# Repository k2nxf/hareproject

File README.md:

# hareproject
The hackable audio and real-time effects (H.A.R.E) project

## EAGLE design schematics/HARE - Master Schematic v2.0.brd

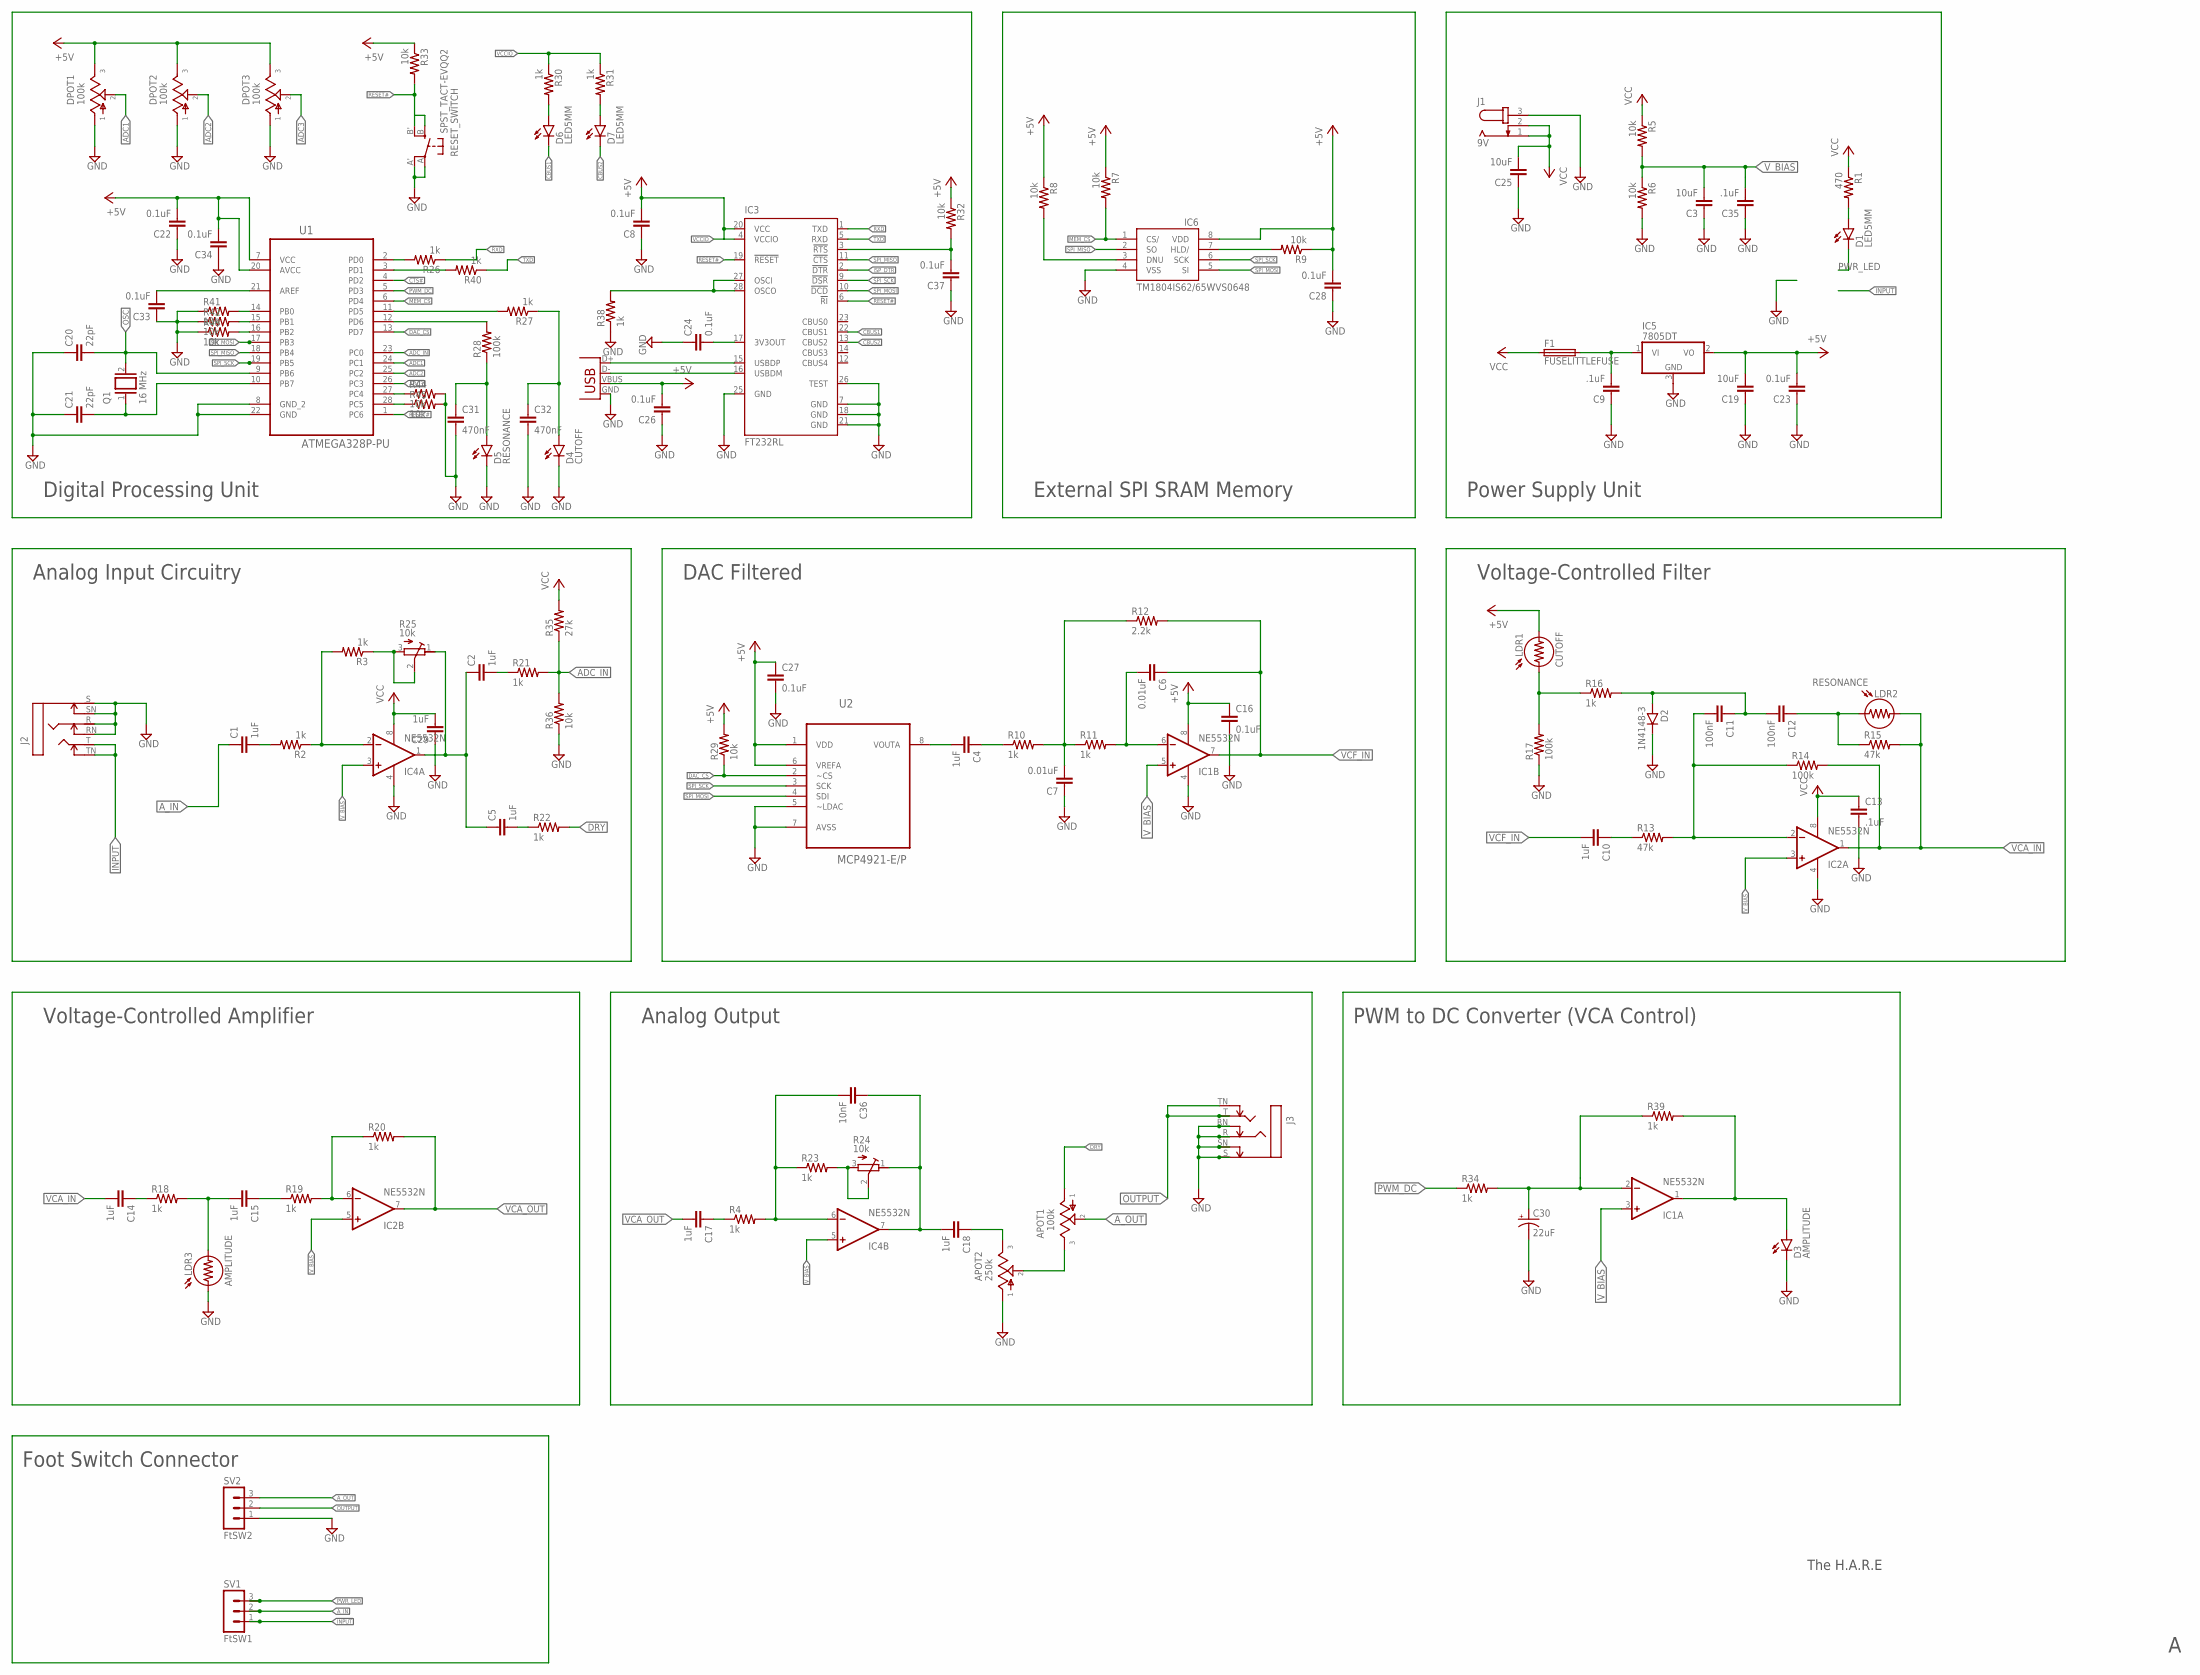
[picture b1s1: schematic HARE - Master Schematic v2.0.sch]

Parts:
APOT1: 100k; 16MM-SQUARE
APOT2: 250k; 16MM-SQUARE
C1, C2, C4, C5, C10, C14, C15, C17, C18, C29: 1uF; C0805K
C3, C19, C25: 10uF; C0805K
C6, C7: 0.01uF; C0805K
C8, C16, C22, C23, C24, C26, C27, C28, C33, C34, C37: 0.1uF; C0805K
C9, C13, C35: .1uF; C0805K
C11, C12: 100nF; C0805K
C20, C21: 22pF; C0805K
C30: 22uF; 050_020_1
C31, C32: 470nF; 072X035
C36: 10nF; C0805K
D1, D6, D7: LED5MM
D2: 1N4148-3; DO35-3
D3: AMPLITUDE; LED5MM
D4: CUTOFF; LED5MM
D5: RESONANCE; LED5MM
DPOT1, DPOT2, DPOT3: 100k; 16MM-SQUARE
F1: FUSELITTLEFUSE; LITTLEFUSE
IC1, IC2, IC4: NE5532N; DIL08
IC3: FT232RL; SSOP28
IC5: 7805DT; TO252
IC6: TM1804IS62/65WVS0648; SO08
J1: 9V; SPC4078
J2, J3: STEREOSW; NMJ6HCD2
LDR1: CUTOFF; LDR338-54C
LDR2: RESONANCE; LDR338-54C
LDR3: AMPLITUDE; LDR338-54C
Q1: 16 MHz; QS
R1: 470; M0805
R2, R3, R4, R10, R11, R16, R18, R19, R20, R21, R22, R23, R26, R27, R30, R31, R34, R38, R39, R40: 1k; R0805
R5, R6, R7, R8, R9: 10k; M0805
R12: 2.2k; R0805
R13, R15: 47k; R0805
R14, R17, R28: 100k; R0805
R24, R25: 10k; RTRIM3314G
R29, R32, R33, R36, R41, R42, R43, R44, R45: 10k; R0805
R35: 27k; R0805
RESET_SWITCH: SPST_TACT-EVQQ2; EVQ-Q2
SV1: FtSW1; MA03-1
SV2: FtSW2; MA03-1
U1: ATMEGA328P-PU; DIP254P762X457-28
U2: MCP4921-E/P; DIP254P762X432-8
X2: USB-B-H

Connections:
+5V: C16.1, C19.2, C22.2, C23.2, C26.2, C27.1, C28.2, C34.2, DPOT1.3, DPOT2.3, DPOT3.3, IC1.8 (V+), IC5.2 (VO), IC6.8 (VDD), LDR1.2, R7.1, R8.1, R9.1, R29.2, R32.1, R33.1, U1.7 (VCC), U1.20 (AVCC), U2.1 (VDD), U2.6 (VREFA), X2.VBUS
+5V1: C33.2, U1.21 (AREF)
ADC1: DPOT1.2, U1.24 (PC1)
ADC2: DPOT2.2, U1.25 (PC2)
ADC3: DPOT3.2, U1.26 (PC3)
ADC_IN: R21.2, R35.1, R36.2, U1.23 (PC0)
A_IN: C1.1, SV1.2
A_OUT: APOT1.2, SV2.3
CBUS1: D6.K (C), IC3.22 (CBUS1)
CBUS2: D7.K (C), IC3.13 (CBUS2)
CTS#: U1.4 (PD2)
DAC_CS: R29.1, U1.13 (PD7), U2.2 (~CS)
DRY: APOT1.1, R22.2
GND: APOT2.1, C3.1, C7.1, C8.1, C9.1, C13.2, C16.2, C19.1, C20.1, C21.1, C22.1, C23.1, C24.1, C25.1, C26.1, C27.2, C28.1, C29.1, C30.-, C31.2, C32.2, C33.1, C34.1, C35.1, C37.1, D2.C, D3.K (C), D4.K (C), D5.K (C), DPOT1.1, DPOT2.1, DPOT3.1, IC1.4 (V-), IC2.4 (V-), IC3.7 (GND), IC3.18 (GND), IC3.21 (GND), IC3.25 (GND), IC3.26 (TEST), IC4.4 (V-), IC5.3 (GND), IC6.4 (VSS), J1.3, J2.R, J2.RN, J2.S, J2.SN, J3.R, J3.RN, J3.S, J3.SN, LDR3.1, R6.2, R17.1, R36.1, R38.1, R41.1, R42.1, R43.1, R44.2, R45.2, RESET_SWITCH.A, RESET_SWITCH.A' (P1), SV2.1, U1.8 (GND_2), U1.22 (GND), U2.5 (~LDAC), U2.7 (AVSS), X2.GND
INPUT: J2.T, J2.TN, SV1.1
ISP_DTR: IC3.2 (!DTR)
MEM_CS: IC6.1 (CS/), R7.2, U1.6 (PD4)
unnamed: D1.A, R1.2
unnamed: IC6.7 (HLD/), R9.2
unnamed: C1.2, R2.2
unnamed: IC4.2 (-IN), R2.1, R3.2
unnamed: C4.2, U2.8 (VOUTA)
unnamed: C4.1, R10.1
unnamed: C5.2, R22.1
unnamed: C30.+, IC1.2 (-IN), R34.2, R39.1
unnamed: C7.2, R10.2, R11.1, R12.1
unnamed: C6.2, IC1.6 (-IN), R11.2
unnamed: IC6.3 (DNU), R8.2
unnamed: D3.A, IC1.1 (OUT), R39.2
unnamed: C10.1, R13.1
unnamed: C11.2, IC2.2 (-IN), R13.2, R14.1
unnamed: C37.2, IC3.3 (!RTS), R32.2
unnamed: C12.1, LDR2.1, R15.1
unnamed: C11.1, C12.2, D2.A, R16.2
unnamed: IC3.27 (OSCI), IC3.28 (OSCO), R38.2
unnamed: LDR1.1, R16.1, R17.2
unnamed: C14.1, R18.1
unnamed: C15.2, LDR3.2, R18.2
unnamed: C15.1, R19.1
unnamed: IC2.6 (-IN), R19.2, R20.1
unnamed: C9.2, F1.2, IC5.1 (VI)
unnamed: R26.2, U1.2 (PD0)
unnamed: C2.2, R21.1
unnamed: C2.1, C5.1, IC4.1 (OUT), R25.1 (E)
unnamed: R40.2, U1.3 (PD1)
unnamed: R41.2, U1.14 (PB0)
unnamed: C17.1, R4.1
unnamed: C36.2, IC4.6 (-IN), R4.2, R23.1
unnamed: R23.2, R24.2 (S), R24.3 (A)
unnamed: C18.2, C36.1, IC4.7 (OUT), R24.1 (E)
unnamed: R42.2, U1.15 (PB1)
unnamed: APOT2.3, C18.1
unnamed: APOT1.3, APOT2.2
unnamed: R43.2, U1.16 (PB2)
unnamed: R3.1, R25.2 (S), R25.3 (A)
unnamed: R44.1, U1.27 (PC4)
unnamed: C21.2, Q1.1, U1.10 (PB7)
unnamed: IC3.15 (USBDP), X2.D+
unnamed: IC3.16 (USBDM), X2.D-
unnamed: C24.2, IC3.17 (3V3OUT)
unnamed: R45.1, U1.28 (PC5)
unnamed: R28.2, U1.12 (PD6)
unnamed: C31.1, D5.A, R28.1
unnamed: R27.2, U1.11 (PD5)
unnamed: C32.1, D4.A, R27.1
unnamed: D6.A, R30.2
unnamed: D7.A, R31.2
OSC: C20.2, Q1.2, U1.9 (PB6)
OUTPUT: J3.T, J3.TN, SV2.2
PWM_DC: R34.1, U1.5 (PD3)
PWR_LED: D1.K (C), SV1.3
RESET#: IC3.6 (!RI), IC3.19 (!RESET), R33.2, RESET_SWITCH.B (S), RESET_SWITCH.B' (S1), U1.1 (PC6)
RXD: IC3.1 (TXD), R26.1
SPI_MISO: IC3.11 (!CTS), IC6.2 (SO), U1.18 (PB4)
SPI_MOSI: IC3.10 (!DCD), IC6.5 (SI), U1.17 (PB3), U2.4 (SDI)
SPI_SCK: IC3.9 (!DSR), IC6.6 (SCK), U1.19 (PB5), U2.3 (SCK)
TXD: IC3.5 (RXD), R40.1
VCA_IN: C14.2, IC2.1 (OUT), LDR2.2, R14.2, R15.2
VCA_OUT: C17.2, IC2.7 (OUT), R20.2
VCC: C13.1, C25.2, C29.2, F1.1, IC2.8 (V+), IC4.8 (V+), J1.1, J1.2, R1.1, R5.1, R35.2
VCCIO: C8.2, IC3.4 (VCCIO), IC3.20 (VCC), R30.1, R31.1
VCF_IN: C6.1, C10.2, IC1.7 (OUT), R12.2
V_BIAS: C3.2, C35.2, IC1.3 (+IN), IC1.5 (+IN), IC2.3 (+IN), IC2.5 (+IN), IC4.3 (+IN), IC4.5 (+IN), R5.2, R6.1

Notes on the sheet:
Power Supply Unit
Digital Processing Unit
Analog Output
Voltage-Controlled Filter
Voltage-Controlled Amplifier
Analog Input Circuitry
DAC Filtered
External SPI SRAM Memory
The H.A.R.E
Foot Switch Connector
PWM to DC Converter (VCA Control)

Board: 2 copper layers, 113 parts (0 on the bottom side), 81 nets, no tracks yet.

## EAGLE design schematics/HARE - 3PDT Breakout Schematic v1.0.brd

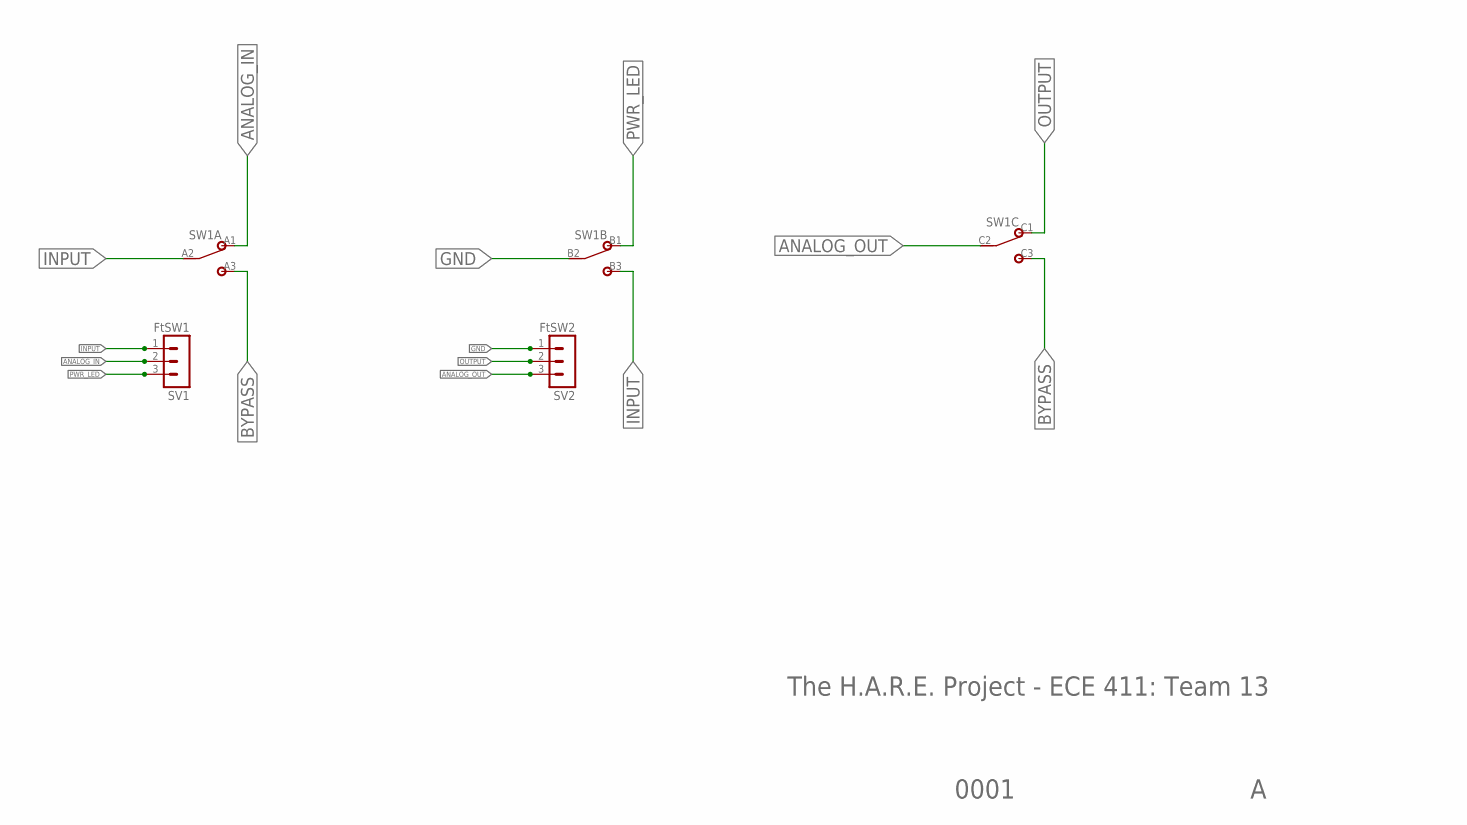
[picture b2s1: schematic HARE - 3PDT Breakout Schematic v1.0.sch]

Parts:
SV1: FtSW1; MA03-1
SV2: FtSW2; MA03-1
SW1: 3PDTBLUE; CHINABLUE

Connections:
ANALOG_IN: SV1.2, SW1.A1 (1)
ANALOG_OUT: SV2.3, SW1.C2 (2)
BYPASS: SW1.A3 (3), SW1.C3 (3)
GND: SV2.1, SW1.B2 (2)
INPUT: SV1.1, SW1.A2 (2), SW1.B3 (3)
OUTPUT: SV2.2, SW1.C1 (1)
PWR_LED: SV1.3, SW1.B1 (1)

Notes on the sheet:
The H.A.R.E. Project - ECE 411: Team 13
0001

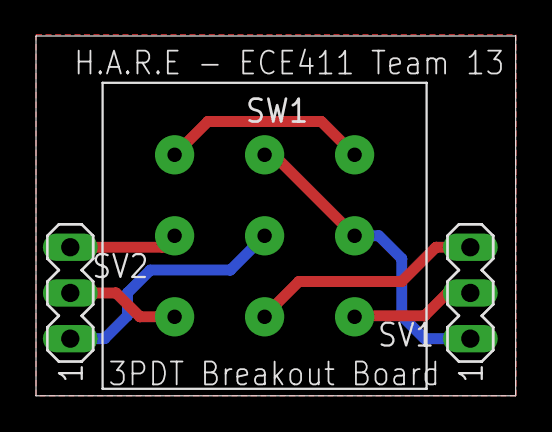
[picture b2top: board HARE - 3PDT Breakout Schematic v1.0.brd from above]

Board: 2 copper layers, 26.7 x 20.0 mm, 3 parts (0 on the bottom side), 7 nets.

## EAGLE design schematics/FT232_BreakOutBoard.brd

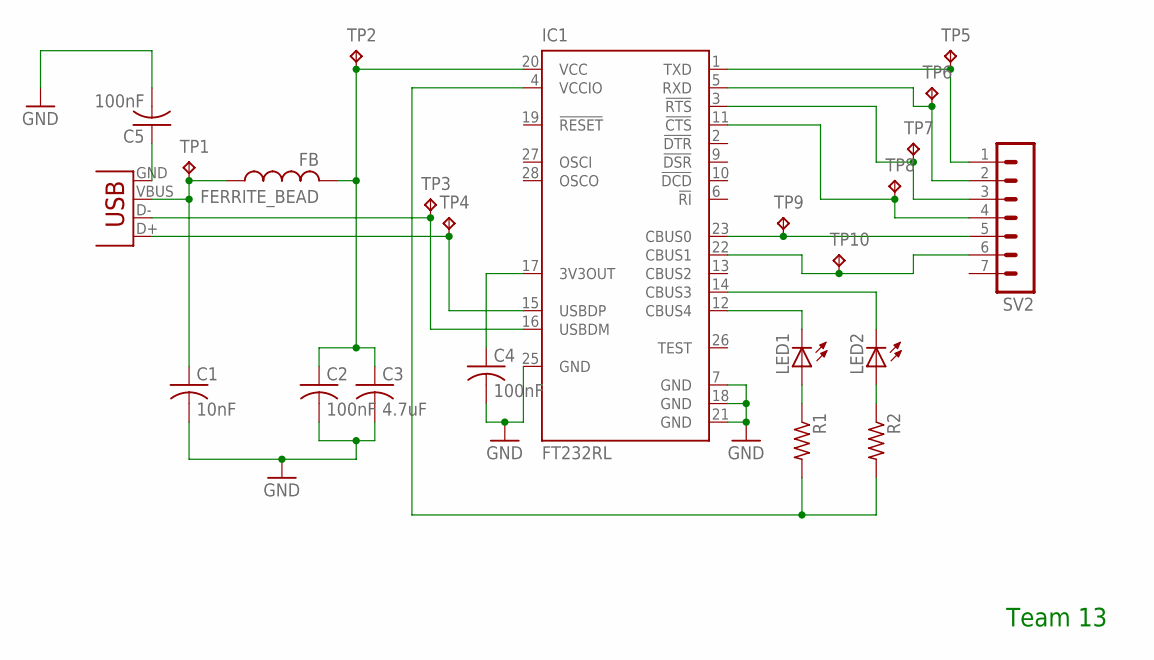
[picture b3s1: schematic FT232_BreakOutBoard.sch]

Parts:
C1: 10nF; C0805
C2, C4, C5: 100nF; C0805
C3: 4.7uF; C0805
FERRITE_BEAD: FB
IC1: FT232RL; SSOP28
LED1, LED2: LEDCHIPLED_0805; CHIPLED_0805
R1, R2: R-US_R0805; R0805
SV2: MA07-1
TP1, TP2, TP3, TP4, TP5, TP6, TP7, TP8, TP9, TP10: TPB1,27; B1,27
X1: USB-B-H

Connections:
DELEETE: IC1.4 (VCCIO), R1.2, R2.2
GND: C1.2, C2.2, C3.2, C4.2, C5.2, IC1.7 (GND), IC1.18 (GND), IC1.21 (GND), IC1.25 (GND)
unnamed: C5.1, X1.GND
unnamed: C4.1, IC1.17 (3V3OUT)
unnamed: IC1.15 (USBDP), TP4.TP, X1.D+
unnamed: IC1.16 (USBDM), TP3.TP, X1.D-
unnamed: IC1.1 (TXD), SV2.1, TP5.TP
unnamed: C1.1, FERRITE_BEAD.P$1 (1), TP1.TP, X1.VBUS
unnamed: IC1.5 (RXD), SV2.2, TP6.TP
unnamed: IC1.3 (!RTS), SV2.3, TP7.TP
unnamed: IC1.11 (!CTS), SV2.4, TP8.TP
unnamed: IC1.23 (CBUS0), SV2.5, TP9.TP
unnamed: LED2.A, R2.1
unnamed: LED1.A, R1.1
unnamed: IC1.22 (CBUS1), SV2.6, TP10.TP
unnamed: IC1.12 (CBUS4), LED1.C
unnamed: IC1.14 (CBUS3), LED2.C
unnamed: C2.1, C3.1, FERRITE_BEAD.P$2 (2), IC1.20 (VCC), TP2.TP

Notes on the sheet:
Team 13

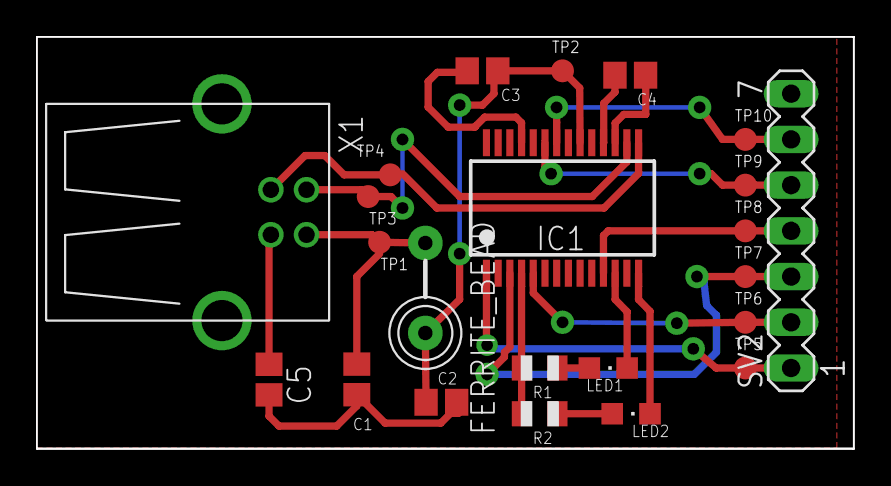
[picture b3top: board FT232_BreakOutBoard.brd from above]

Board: 2 copper layers, 45.4 x 22.9 mm, 23 parts (0 on the bottom side), 18 nets.

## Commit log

2017-10-08 adding new files and folders.
2017-10-08 adding image
2017-10-08 Created a license document
    May need to be cleaned a little, but its a license....so who cares
2017-10-08 just adding folders
2017-10-08 CODE_OF_CONDUCT.cmd
    For the community
2017-10-08 Rename CODE_OF_CONDUCT.md to CODE_OF_CONDUCT
2017-10-08 Adding initial delay effect program
2017-10-08 Adding initial effects
2017-10-09 VCF simulation and BA4560 Spice model
2017-10-12 Updating feature layout graphic
2017-10-19 Adding initial Eagle schematic and board layout
2017-10-19 updating schematic
2017-10-22 Upload FT232R Breakout Board
2017-10-22 updated schematic with analog modules
2017-10-22 Updated schematic and board layout
2017-10-24 arduino code to test PWM control of analog modules
2017-10-25 Completed schematic update
2017-10-25 Updating first schematic build
2017-10-25 Update Schematic
2017-10-25 Update board layout
    Update board layout to match schematic updates.
2017-10-25 Connected FT232 to reset switch.
2017-10-27 Added DAC_OUT node to schematic
2017-10-27 updated breakout board layout and schematic
2017-10-28 Added effect routines for testing with modules (clean, delay, oBITerator)
2017-11-02 Uploaded GANTT Chart of project schedule
2017-11-02 Updated clean code with new PWM mode
2017-11-02 Updated FT232 break-out board with corrected USB connector and larger vias
2017-11-02 FT232 break-out board update
2017-11-02 Fixed ERC errors
2017-11-02 Resolved errors and most warnings in ERC
2017-11-02 Cleaning up dead files
2017-11-03 update breakout board with all loins connected
2017-11-05 ^O
    This is the block diagram homework assignment. Needs to be added to the wiki.
    This is the block diagram homework assignment. Needs to be added to the wiki.
2017-11-06 Added PWMDAC and DAC filter measurements.
2017-11-06 Added PWMDAC filter measurements
2017-11-06 Deleted BMPs
2017-11-06 Added External Memory Device
    Added External SPI EEPROM Memory Device - CAT25512 (AT25512)
2017-11-06 Switch memory chip to SRAM
2017-11-06 fix WP pin on SRAM chip to DNU
2017-11-06 Added measurements for PWMDAC and analog in/out.
2017-11-09 Added bare metal version of clean (main.c)
2017-11-09 Created master schematic and board layout
2017-11-09 Updated test code
2017-11-09 Updated master schematic
2017-11-10 Started the eagle layout and fixed a few errors in the schematic
2017-11-10 added OSH Park DRC rules to schematics folder
2017-11-10 The beginning of a board. Need to route power and move some resistors and capacitors
2017-11-12 First pass at board layout and updated schematic
2017-11-13 Updated clean function with ADC and PWM init routines
2017-11-13 Updated clean program with ADC and PWM capabilities
2017-11-13 Added team number to master schematic
2017-11-13 Zack DiD it!
2017-11-13 Added IC bypass caps
2017-11-14 Updated clean effect and added utilities.h
2017-11-14 ZACK DEFINITELY DID ITgit add schematics/HARE\ -\ Master\ Schematic\ v1.0.sch schematics/HARE\ -\ Master\ Schematic\ v1.0.brd !
2017-11-14 Adding initial routing for footswitch cutout
2017-11-14 Updated VCF control values
2017-11-14 Cleaning house
2017-11-14 attempting to correct
2017-11-14 Updated VCF and PWM LEDs filters
2017-11-14 Updated VCF component values and added PWM LED filters
2017-11-14 Updated the board file to include cutout for foot switch and some greenburg recommendations
2017-11-14 adding gm-jack libraries
2017-11-14 fixed the board and schematic files
2017-11-14 no DRC errors in board file
2017-11-14 fixed a couple ERC issues
2017-11-14 Cleaned up delay folder from redundant folders
2017-11-14 PWM-to-DC converter added for VCA control, VCF changes fixed, and fuse added
2017-11-14 Added filtering cap to analog output circuitry
2017-11-14 Added high frequency filter cap to analog output circuitry
2017-11-15 Adding 3PDT breakout board schematic and layout
2017-11-15 Completed routing high frequency filter caps
2017-11-15 adapting 3PDT breakout board to mate with HARE main board
2017-11-15 Correctly placed the 3PDT switch connectors to mate with the main board
2017-11-15 new chip and bootloader
2017-11-15 Added SPI oscilloscope measurements for SCK and MOSI pins (MCP4921 communication)
2017-11-15 Updated clean effect with SPI routines
2017-11-16 Updated dac_write function with byte concatenation
2017-11-16 Added SuperBun Image to brd
2017-11-16 Add IS62 Chip
2017-11-16 Add files via upload
    Bottom layer board image
2017-11-16 How to add image to board layout
    Brief instructions for adding a bitmap image to silkscreen layer
2017-11-16 Finished Board layout without art
2017-11-16 finished board layout with HAREBUN artwork on bottom of board
2017-11-16 Shrank the size of the daughter board for the footswitch
2017-11-16 REV 1 for HARE ready for tapeout
2017-11-16 REV 1 of HARE with correct artwork ready for tapeout
2017-11-16 Added some define statements to utilities.h for easier debugging.
2017-11-26 Add files via upload
    Parts Ordered 11/26/17
2017-12-06 Adding some additional documents and measuremnts
2017-12-07 Latest clean code update. Photos of prototypes also uploaded.
2017-12-07 uploading test plan and completed INPUT TEST
2017-12-10 Updated with Resolved Comm. Issues
    TXD/RXD switched, CTS and RTS removed from reset along with R37 and C37, set up correct ISCP for SPI boot loading from FT232, Tied VCCIO to 5V and changed the name of the board
2017-12-10 updated to match sch
